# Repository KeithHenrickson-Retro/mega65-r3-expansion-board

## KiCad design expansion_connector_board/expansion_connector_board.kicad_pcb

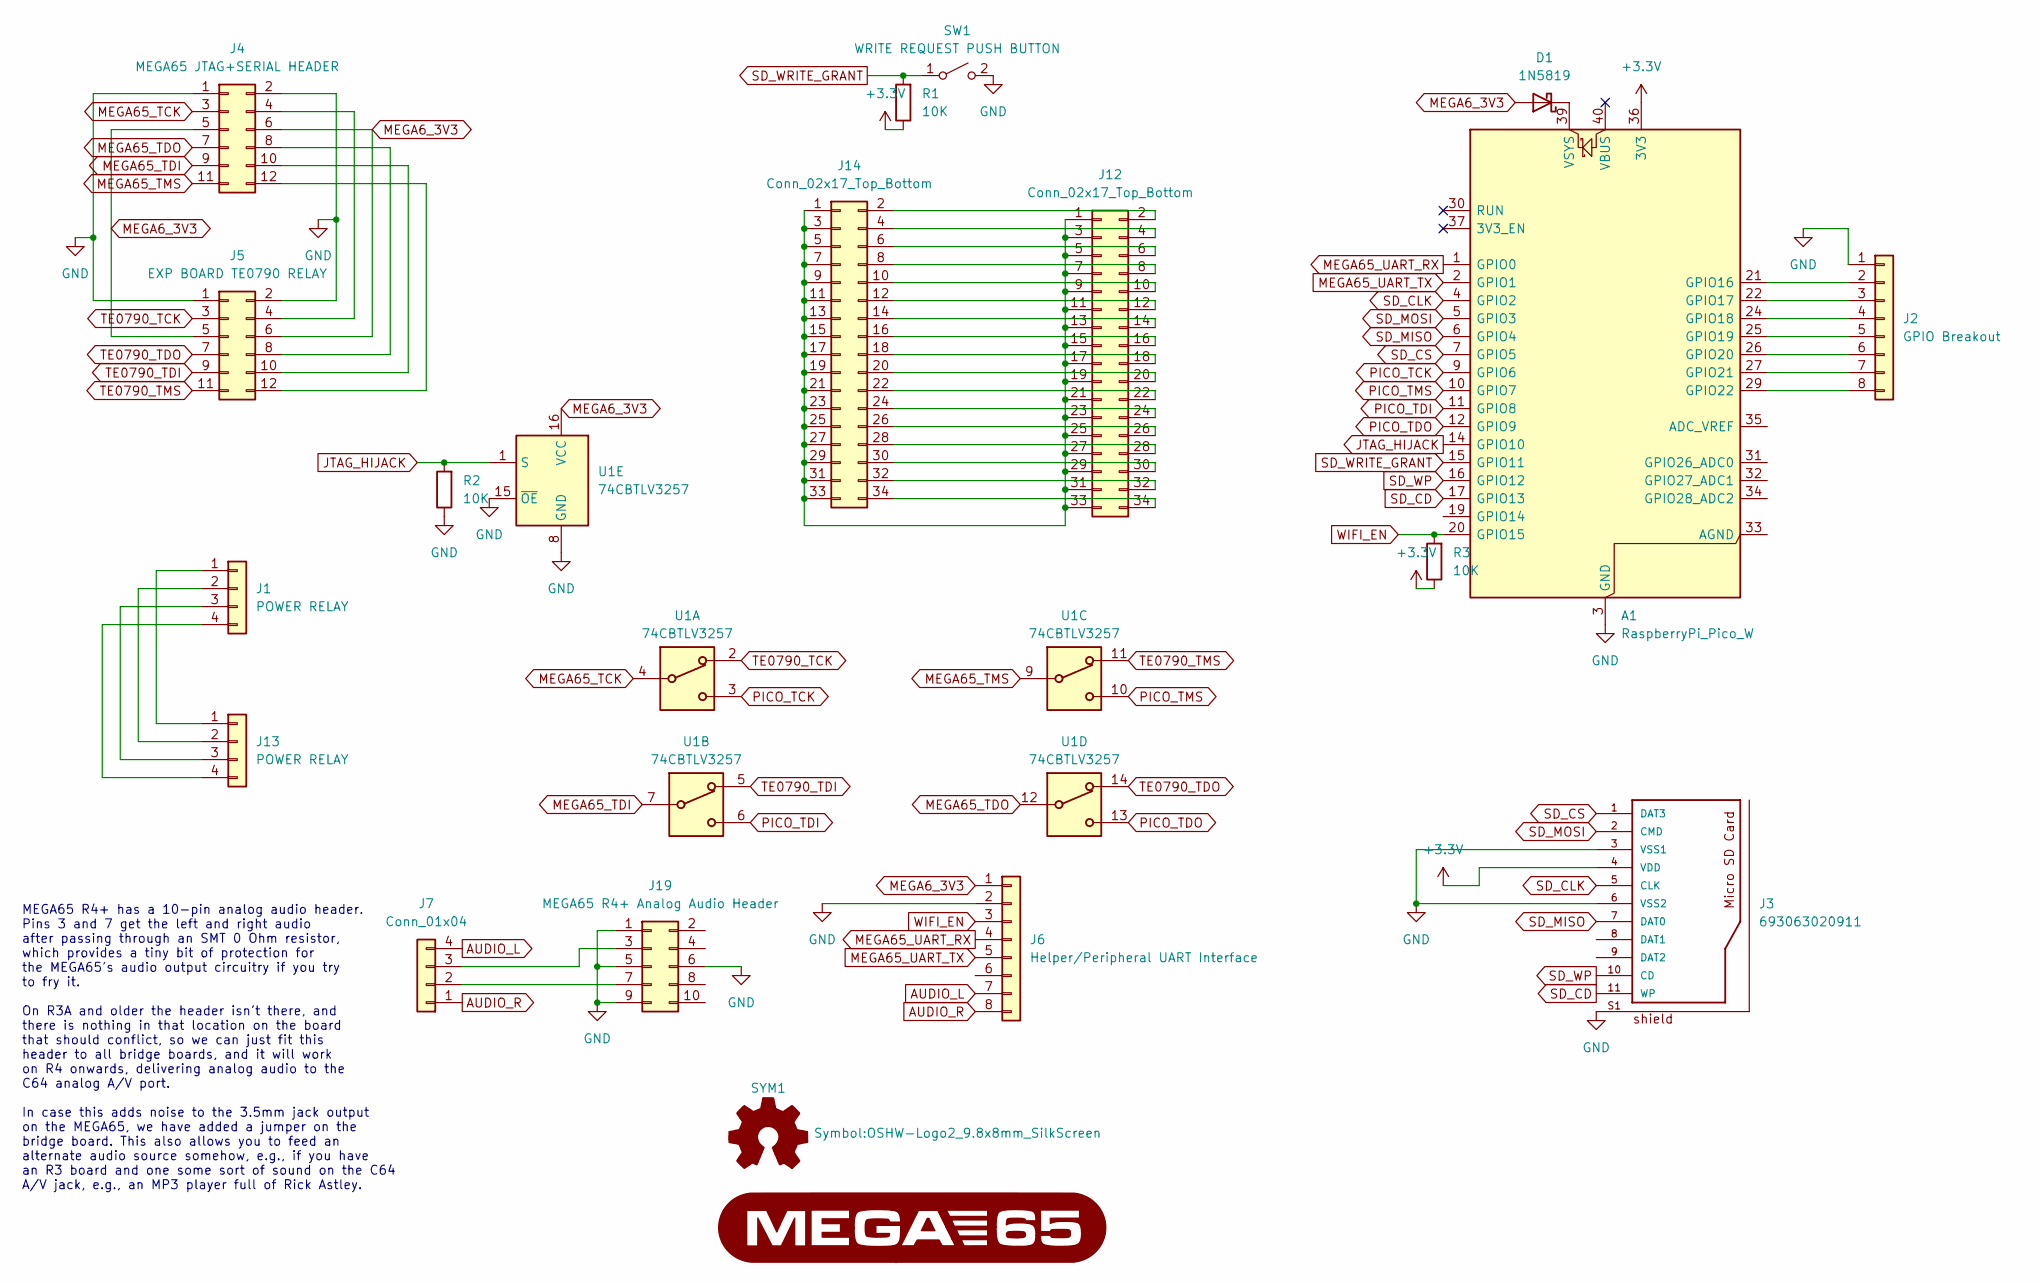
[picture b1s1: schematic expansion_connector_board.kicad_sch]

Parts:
A1: RaspberryPi_Pico_W; RaspberryPi_Pico_W_SMD_HandSolder
D1: 1N5819; D_DO-41_SOD81_P10.16mm_Horizontal
G1: LOGO; MEGA65-logo
J1, J13: POWER RELAY; PinSocket_1x04_P2.54mm_Vertical
J2: GPIO Breakout; PinHeader_1x08_P2.54mm_Vertical
J3: 693063020911
J4: MEGA65 JTAG+SERIAL HEADER; PinSocket_2x06_P2.54mm_Vertical
J5: EXP BOARD TE0790 RELAY; PinSocket_2x06_P2.54mm_Vertical
J6: Helper/Peripheral UART Interface; PinSocket_1x08_P2.54mm_Vertical
J7: Conn_01x04; PinHeader_1x04_P2.54mm_Vertical
J12, J14: Conn_02x17_Top_Bottom; PinSocket_2x17_P2.54mm_Vertical
J19: MEGA65 R4+ Analog Audio Header; PinSocket_2x05_P2.54mm_Vertical
R1, R2, R3: 10K; R_Axial_DIN0207_L6.3mm_D2.5mm_P10.16mm_Horizontal
SW1: WRITE REQUEST PUSH BUTTON; TE_2-1825027-0
SYM1: Logo_Open_Hardware_Small; OSHW-Logo2_9.8x8mm_SilkScreen
U1: 74CBTLV3257; SOIC-16_3.9x9.9mm_P1.27mm

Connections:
+3.3V: A1.36 (3V3), J3.4 (VDD), R1.1, R3.1
AUDIO_L: J6.7, J7.4
AUDIO_R: J6.8, J7.1
GND: A1.3 (GND), A1.8 (GND), A1.13 (GND), A1.18 (GND), A1.23 (GND), A1.28 (GND), A1.38 (GND), J2.1, J3.3 (VSS1), J3.6 (VSS2), J3.S1, J3.S2, J3.S3, J3.S4, J4.1, J4.2, J5.1, J5.2, J6.2, J19.1, J19.5, J19.6, J19.9, R2.1, SW1.2 (B), U1.8 (GND), U1.15 (~OE)
JTAG_HIJACK: A1.14 (GPIO10), R2.2, U1.1 (S)
MEGA6_3V3: D1.2 (A), J4.5, J4.6, J5.5, J5.6, J6.1, U1.16 (VCC)
MEGA65_TCK: J4.3, U1.4
MEGA65_TDI: J4.9, U1.7
MEGA65_TDO: J4.7, U1.12
MEGA65_TMS: J4.11, U1.9
MEGA65_UART_RX: A1.1 (GPIO0), J6.4
MEGA65_UART_TX: A1.2 (GPIO1), J6.5
unnamed: A1.21 (GPIO16), J2.2
unnamed: A1.22 (GPIO17), J2.3
unnamed: A1.24 (GPIO18), J2.4
unnamed: A1.25 (GPIO19), J2.5
unnamed: A1.26 (GPIO20), J2.6
unnamed: A1.27 (GPIO21), J2.7
unnamed: A1.29 (GPIO22), J2.8
unnamed: A1.39 (VSYS), D1.1 (K)
unnamed: J1.1, J13.1
unnamed: J1.2, J13.2
unnamed: J1.3, J13.3
unnamed: J1.4, J13.4
unnamed: J4.4, J5.4
unnamed: J4.8, J5.8
unnamed: J4.10, J5.10
unnamed: J4.12, J5.12
unnamed: J12.1, J12.3, J12.5, J12.7, J12.9, J12.11, J12.13, J12.15, J12.17, J12.19, J12.21, J12.23, J12.25, J12.27, J12.29, J12.31, J12.33, J14.1, J14.3, J14.5, J14.7, J14.9, J14.11, J14.13, J14.15, J14.17, J14.19, J14.21, J14.23, J14.25, J14.27, J14.29, J14.31, J14.33
unnamed: J12.2, J14.2
unnamed: J12.4, J14.4
unnamed: J12.6, J14.6
unnamed: J12.8, J14.8
unnamed: J12.10, J14.10
unnamed: J12.12, J14.12
unnamed: J12.14, J14.14
unnamed: J12.16, J14.16
unnamed: J12.18, J14.18
unnamed: J12.20, J14.20
unnamed: J12.22, J14.22
unnamed: J12.24, J14.24
unnamed: J12.26, J14.26
unnamed: J12.28, J14.28
unnamed: J12.30, J14.30
unnamed: J12.32, J14.32
unnamed: J12.34, J14.34
unnamed: J7.3, J19.3
unnamed: J7.2, J19.7
PICO_TCK: A1.9 (GPIO6), U1.3
PICO_TDI: A1.11 (GPIO8), U1.6
PICO_TDO: A1.12 (GPIO9), U1.13
PICO_TMS: A1.10 (GPIO7), U1.10
SD_CD: A1.17 (GPIO13), J3.11 (WP)
SD_CLK: A1.4 (GPIO2), J3.5 (CLK)
SD_CS: A1.7 (GPIO5), J3.1 (DAT3)
SD_MISO: A1.6 (GPIO4), J3.7 (DAT0)
SD_MOSI: A1.5 (GPIO3), J3.2 (CMD)
SD_WP: A1.16 (GPIO12), J3.10 (CD)
SD_WRITE_GRANT: A1.15 (GPIO11), R1.2, SW1.1 (A)
TE0790_TCK: J5.3, U1.2
TE0790_TDI: J5.9, U1.5
TE0790_TDO: J5.7, U1.14
TE0790_TMS: J5.11, U1.11
WIFI_EN: A1.20 (GPIO15), J6.3, R3.2

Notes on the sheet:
MEGA65 R4+ has a 10-pin analog audio header. Pins 3 and 7 get the left and right audio after passing through an SMT 0 Ohm resistor, which provides a tiny bit of protection for the MEGA65's audio output circuitry if you try to fry it. On R3A and older the header isn't there, and there is nothing in 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

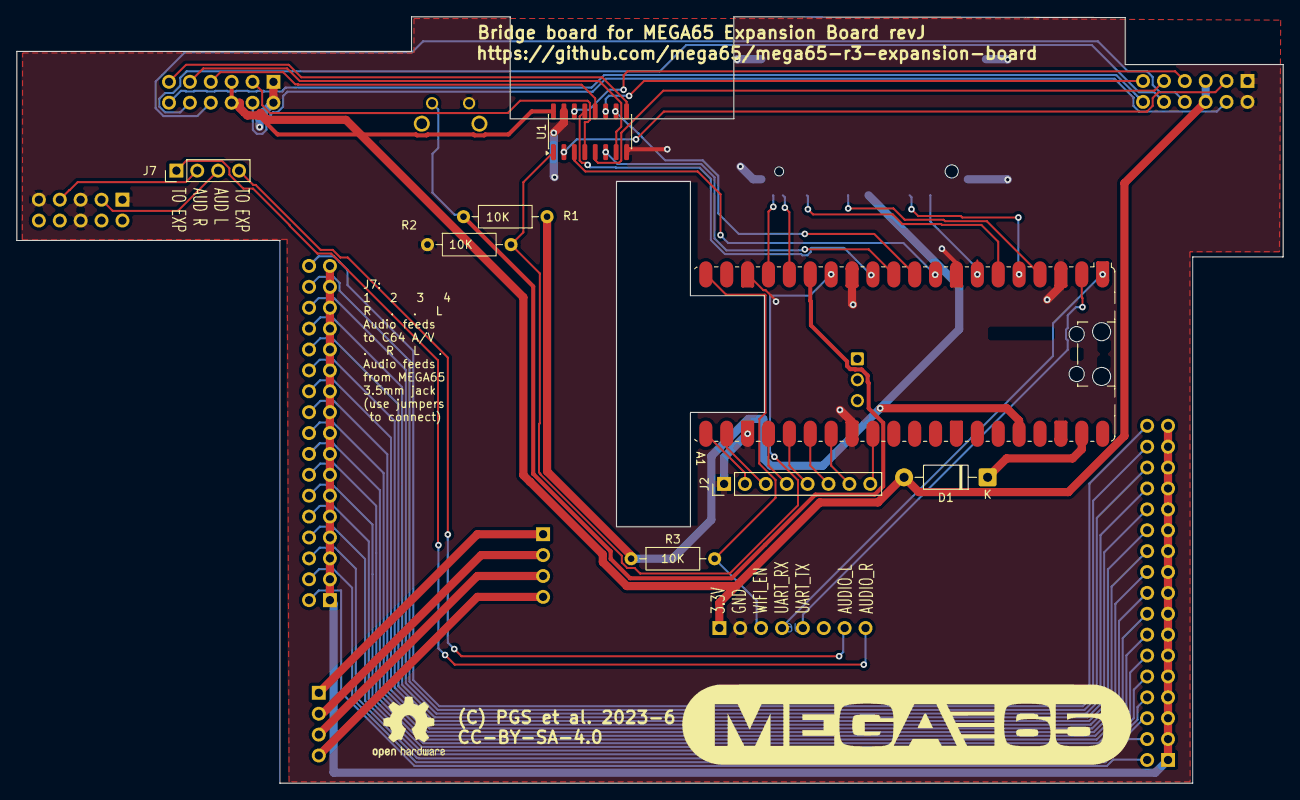
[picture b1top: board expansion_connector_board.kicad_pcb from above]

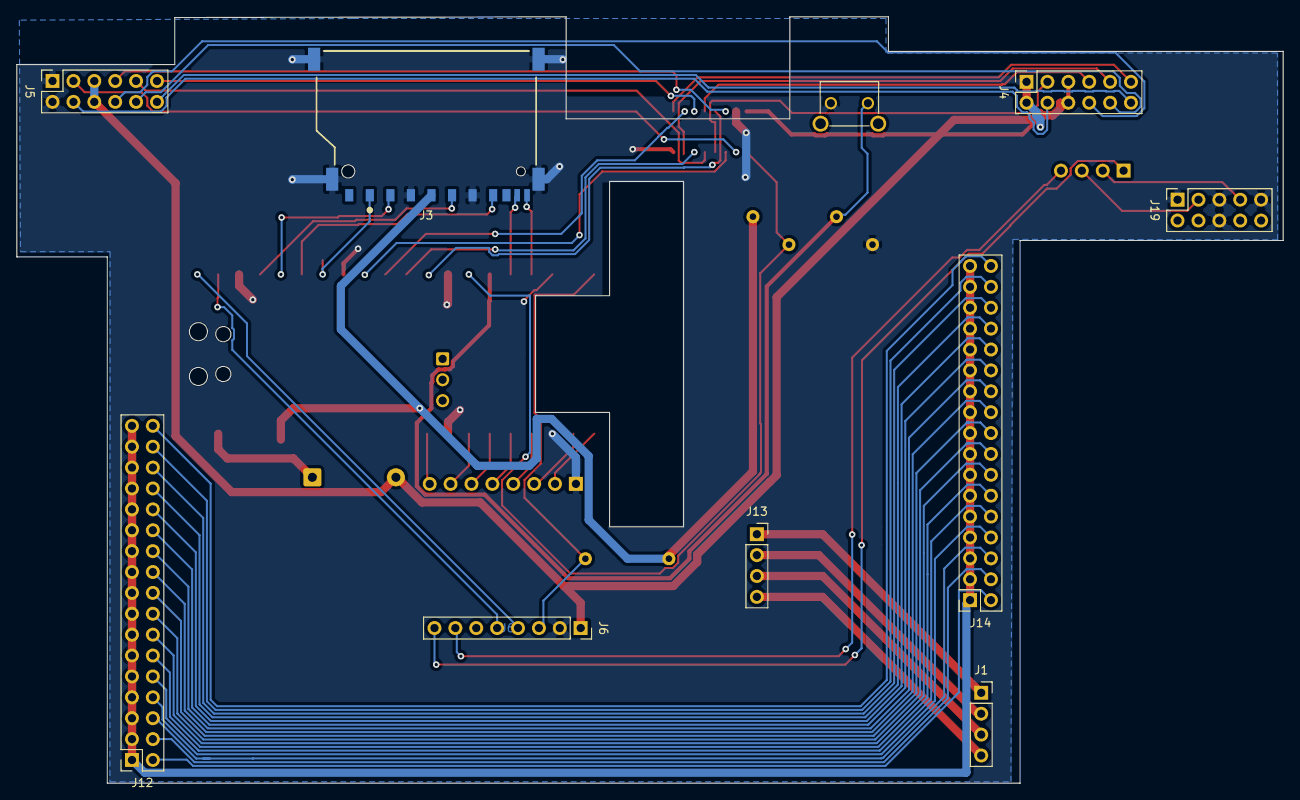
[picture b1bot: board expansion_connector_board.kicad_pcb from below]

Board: 2 copper layers, 154.0 x 93.2 mm, 21 parts (10 on the bottom side), 64 nets.

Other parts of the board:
STACK_PREVIEW: STACK_PREVIEW

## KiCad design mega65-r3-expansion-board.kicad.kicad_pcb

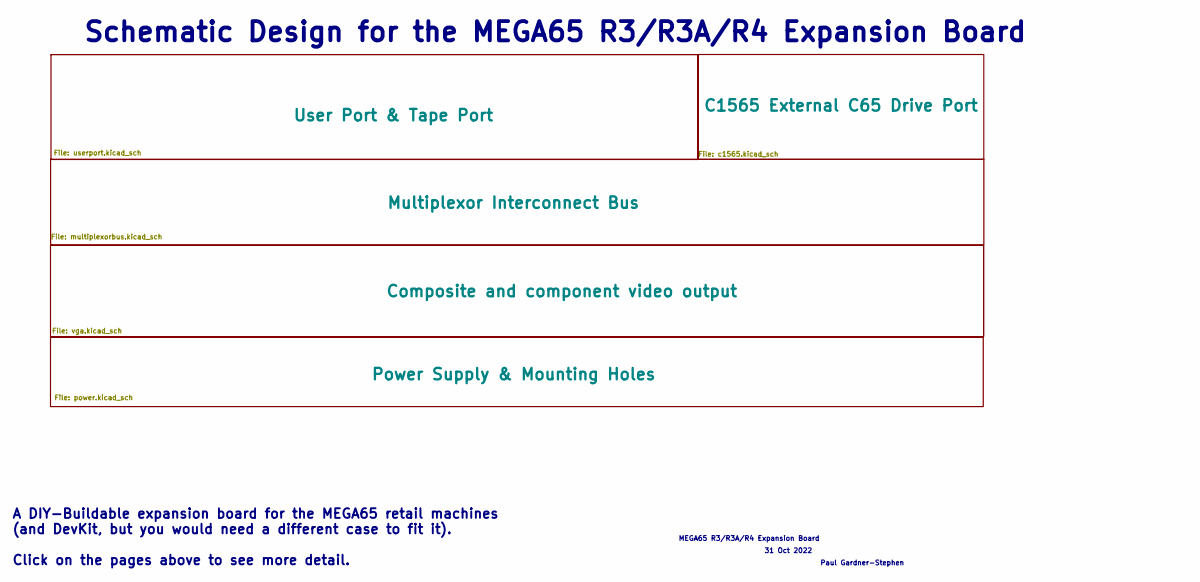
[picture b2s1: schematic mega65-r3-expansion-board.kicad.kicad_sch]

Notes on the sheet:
Paul Gardner-Stephen
A DIY-Buildable expansion board for the MEGA65 retail machines (and DevKit, but you would need a different case to fit it). Click on the pages above to see more detail.
31 Oct 2022
MEGA65 R3/R3A/R4 Expansion Board
Schematic Design for the MEGA65 R3/R3A/R4 Expansion Board

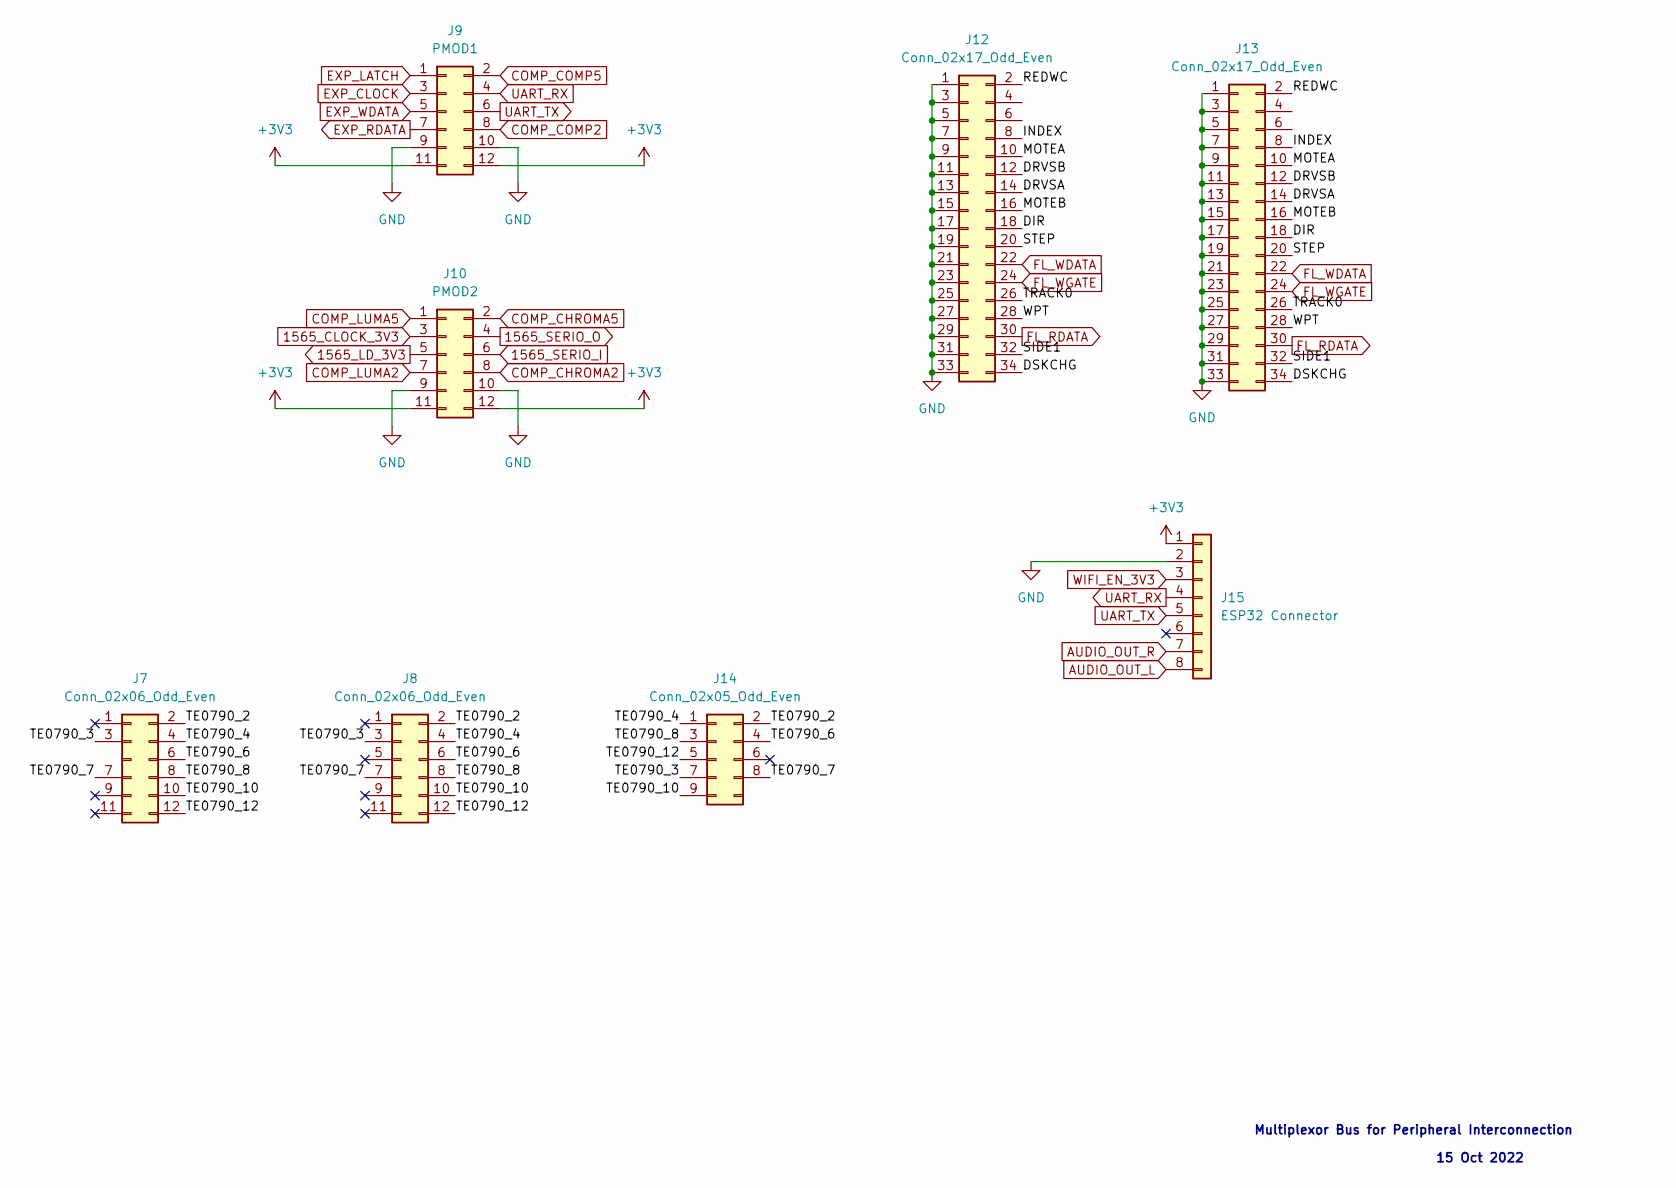
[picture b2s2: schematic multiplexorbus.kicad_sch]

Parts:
J7, J8: Conn_02x06_Odd_Even; PinHeader_2x06_P2.54mm_Vertical
J9: PMOD1; PinSocket_2x06_P2.54mm_Horizontal
J10: PMOD2; PinSocket_2x06_P2.54mm_Horizontal
J12, J13: Conn_02x17_Odd_Even; PinHeader_2x17_P2.54mm_Vertical
J14: Conn_02x05_Odd_Even; PinHeader_2x05_P2.54mm_Vertical
J15: ESP32 Connector; PinHeader_1x08_P2.54mm_Vertical

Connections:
1565_CLOCK_3V3: J10.3
1565_LD_3V3: J10.5
1565_SERIO_I: J10.6
1565_SERIO_O: J10.4
+3V3: J9.11, J9.12, J10.11, J10.12, J15.1
/Multiplexor Interconnect Bus/DIR: J12.18, J13.18
/Multiplexor Interconnect Bus/DRVSA: J12.14, J13.14
/Multiplexor Interconnect Bus/DRVSB: J12.12, J13.12
/Multiplexor Interconnect Bus/DSKCHG: J12.34, J13.34
/Multiplexor Interconnect Bus/INDEX: J12.8, J13.8
/Multiplexor Interconnect Bus/MOTEA: J12.10, J13.10
/Multiplexor Interconnect Bus/MOTEB: J12.16, J13.16
/Multiplexor Interconnect Bus/REDWC: J12.2, J13.2
/Multiplexor Interconnect Bus/SIDE1: J12.32, J13.32
/Multiplexor Interconnect Bus/STEP: J12.20, J13.20
/Multiplexor Interconnect Bus/TE0790_2: J7.2, J8.2, J14.2
/Multiplexor Interconnect Bus/TE0790_3: J7.3, J8.3, J14.7
/Multiplexor Interconnect Bus/TE0790_4: J7.4, J8.4, J14.1
/Multiplexor Interconnect Bus/TE0790_6: J7.6, J8.6, J14.4
/Multiplexor Interconnect Bus/TE0790_7: J7.7, J8.7, J14.8
/Multiplexor Interconnect Bus/TE0790_8: J7.8, J8.8, J14.3
/Multiplexor Interconnect Bus/TE0790_10: J7.10, J8.10, J14.9
/Multiplexor Interconnect Bus/TE0790_12: J7.12, J8.12, J14.5
/Multiplexor Interconnect Bus/TRACK0: J12.26, J13.26
/Multiplexor Interconnect Bus/WPT: J12.28, J13.28
AUDIO_OUT_L: J15.8
AUDIO_OUT_R: J15.7
COMP_CHROMA2: J10.8
COMP_CHROMA5: J10.2
COMP_LUMA2: J10.7
COMP_LUMA5: J10.1
FL_RDATA: J12.30, J13.30
FL_WDATA: J12.22, J13.22
FL_WGATE: J12.24, J13.24
GND: J9.9, J9.10, J10.9, J10.10, J12.1, J12.3, J12.5, J12.7, J12.9, J12.11, J12.13, J12.15, J12.17, J12.19, J12.21, J12.23, J12.25, J12.27, J12.29, J12.31, J12.33, J13.1, J13.3, J13.5, J13.7, J13.9, J13.11, J13.13, J13.15, J13.17, J13.19, J13.21, J13.23, J13.25, J13.27, J13.29, J13.31, J13.33, J15.2; also elsewhere on the board
UART_RX: J9.4, J15.4
UART_TX: J9.6, J15.5
WIFI_EN_3V3: J15.3

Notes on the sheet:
Multiplexor Bus for Peripheral Interconnection
15 Oct 2022

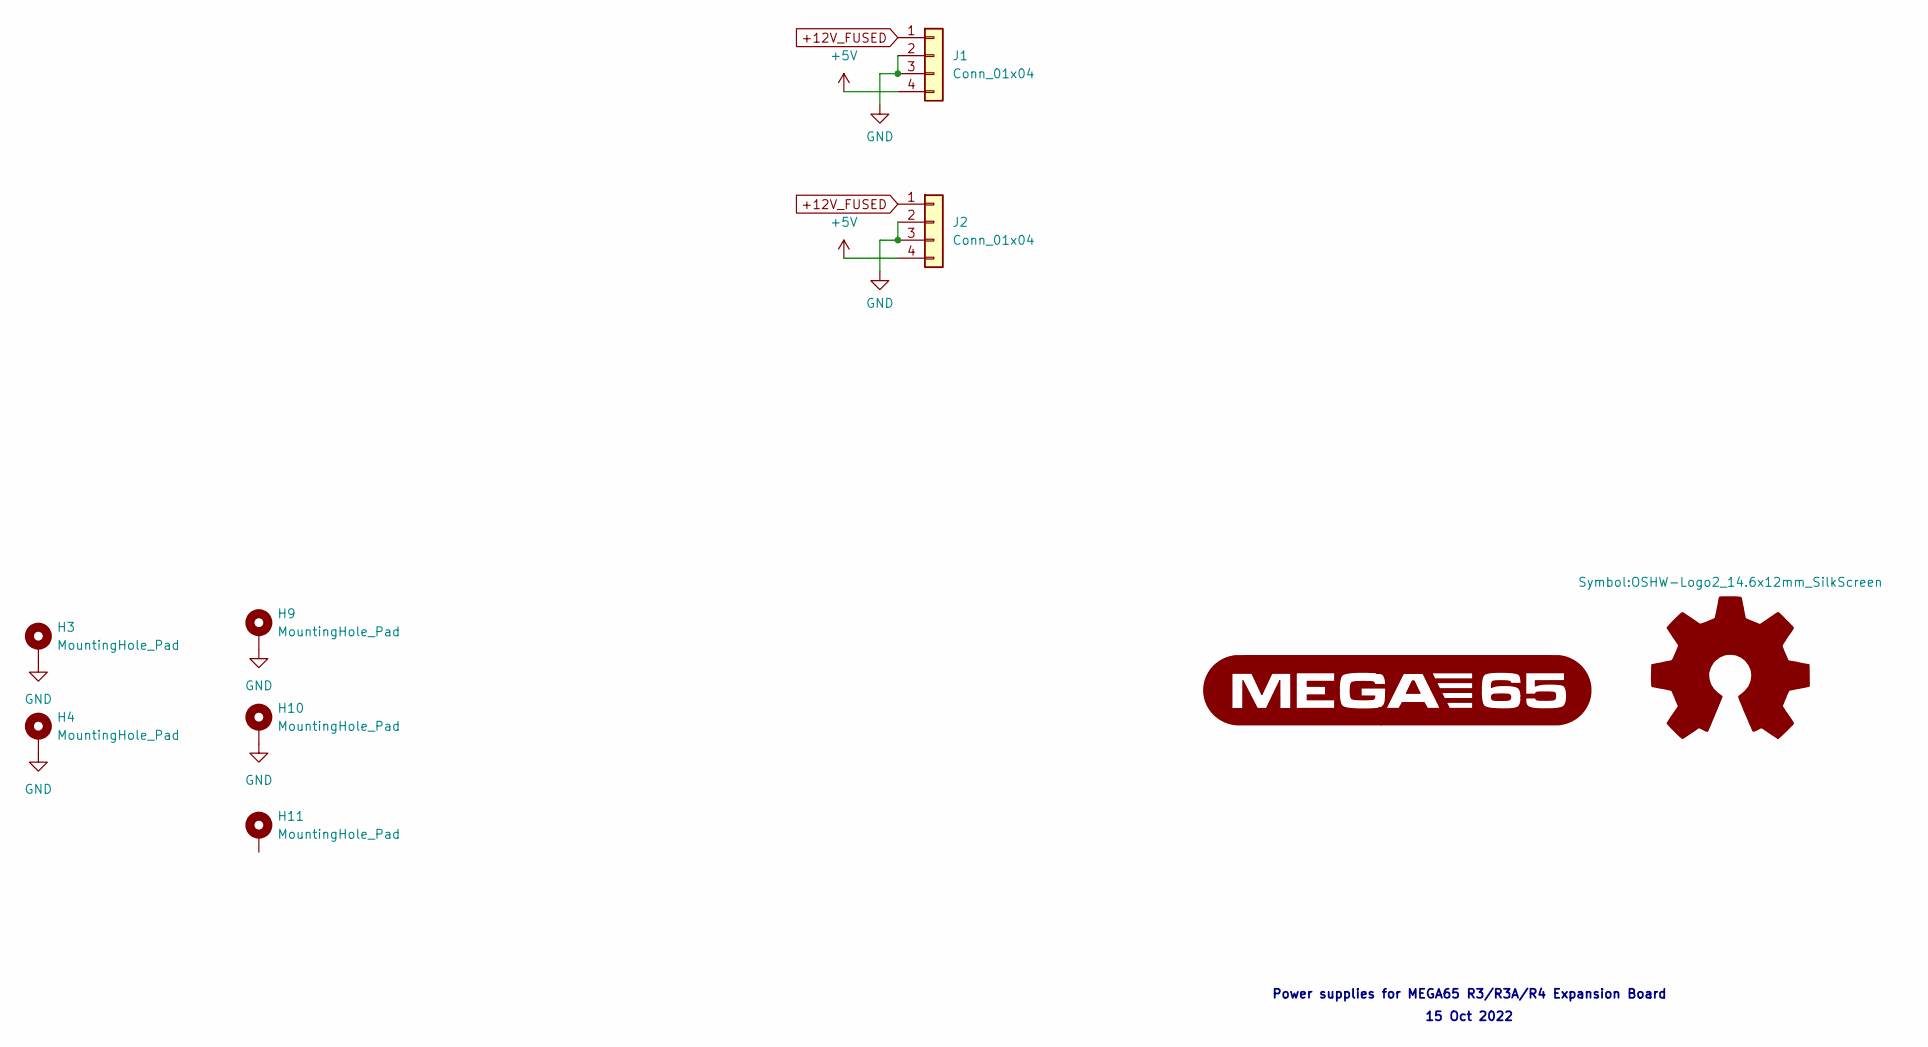
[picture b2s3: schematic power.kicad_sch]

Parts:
H3, H4, H9, H10, H11: MountingHole_Pad; MountingHole_3.2mm_M3_DIN965_Pad
J1, J2: Conn_01x04; FloppyPower
LOGO1: Logo_Open_Hardware_Large; OSHW-Logo2_14.6x12mm_SilkScreen

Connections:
+5V: J1.4, J2.4
+12V_FUSED: J1.1, J2.1
GND: H3.1 (1_1), H4.1 (1_1), H9.1 (1_1), H10.1 (1_1), J1.2, J1.3, J2.2, J2.3; also elsewhere on the board

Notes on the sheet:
Power supplies for MEGA65 R3/R3A/R4 Expansion Board
15 Oct 2022

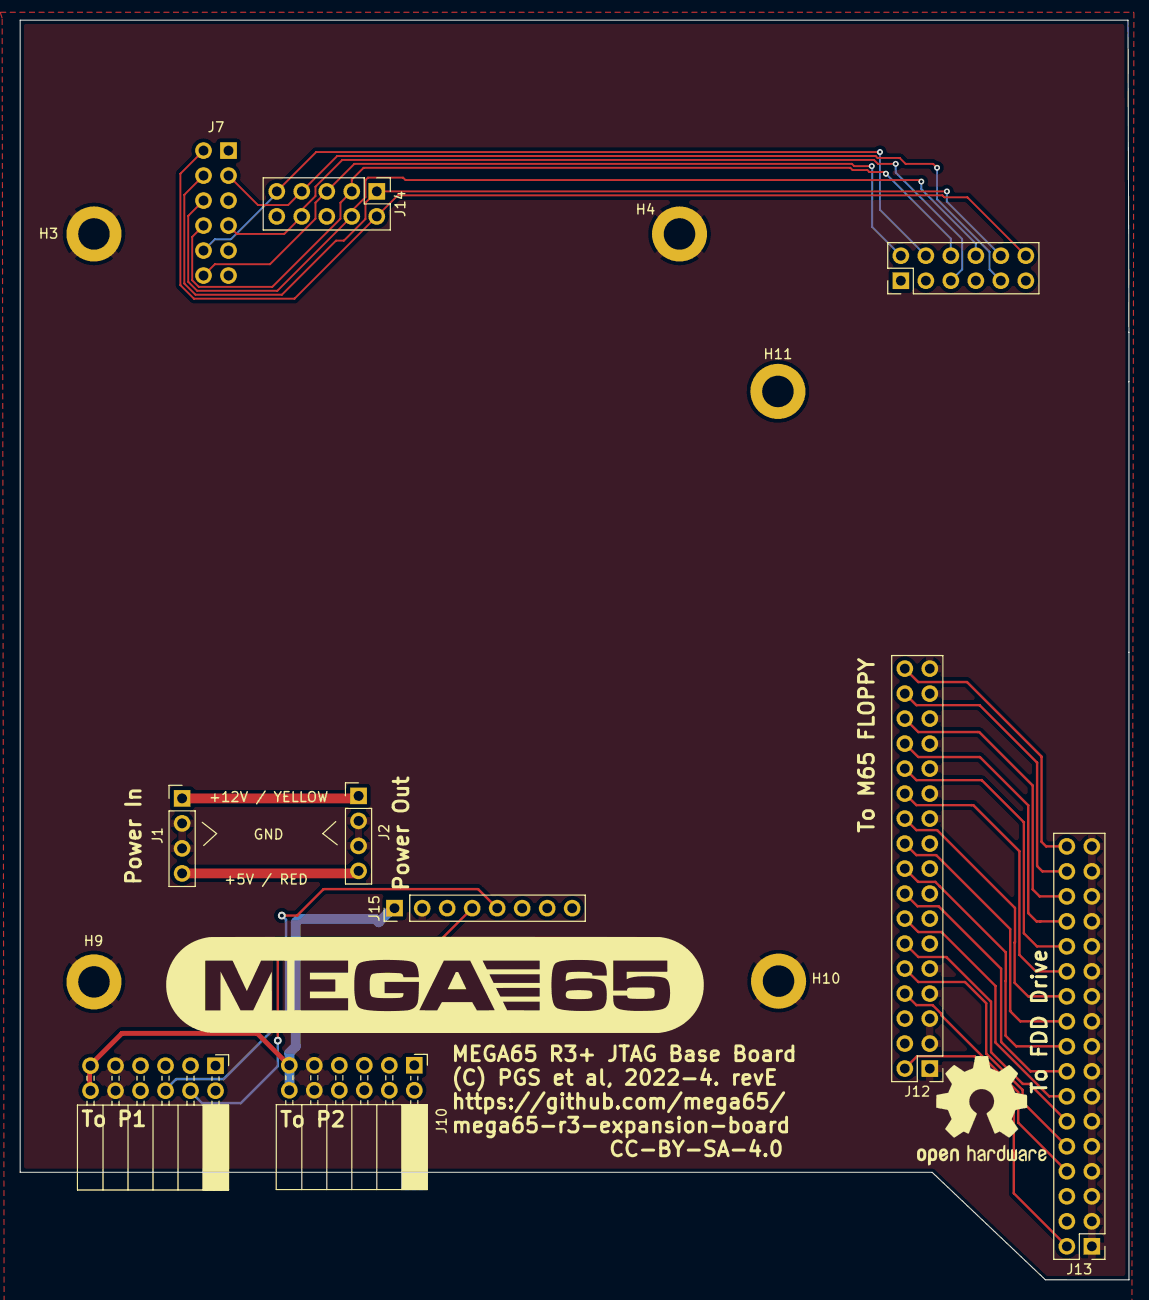
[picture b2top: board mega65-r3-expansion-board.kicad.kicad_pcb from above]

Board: 2 copper layers, 112.7 x 128.0 mm, 15 parts (1 on the bottom side), 27 nets.

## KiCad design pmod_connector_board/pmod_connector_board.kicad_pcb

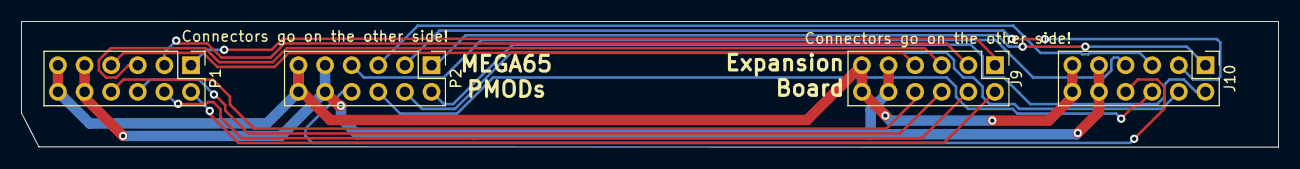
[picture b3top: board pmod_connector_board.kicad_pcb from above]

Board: 2 copper layers, 120.0 x 12.0 mm, 4 parts (0 on the bottom side), 18 nets.

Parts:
J9, J10: Conn_02x06_Top_Bottom; PinHeader_2x06_P2.54mm_Vertical
P1, P2: Conn_02x06_Top_Bottom; PinHeader_2x06_P2.54mm_Vertical

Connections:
+3V3: J9.6, J9.12, J10.6, J10.12, P1.6, P1.12, P2.6, P2.12
GND: J9.5, J9.11, J10.5, J10.11, P1.5, P1.11, P2.5, P2.11
unnamed: J9.1, P1.1
unnamed: J9.2, P1.2
unnamed: J9.3, P1.3
unnamed: J9.4, P1.4
unnamed: J9.7, P1.7
unnamed: J9.8, P1.8
unnamed: J9.9, P1.9
unnamed: J9.10, P1.10
unnamed: J10.1, P2.1
unnamed: J10.2, P2.2
unnamed: J10.3, P2.3
unnamed: J10.4, P2.4
unnamed: J10.7, P2.7
unnamed: J10.8, P2.8
unnamed: J10.9, P2.9
unnamed: J10.10, P2.10

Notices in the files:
expansion_connector_board/expansion_connector_board.kicad_pcb:
CC-BY-SA-4.0
pmod_connector_board/pmod_connector_board.kicad_pcb:
(C) Paul Gardner-Stephen 2024, CC-BY 4.0
